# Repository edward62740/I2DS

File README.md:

# Internal Intruder Detection System (I<sup>2</sup>DS)

## Overview
This is a sub-GHz proprietary security sensor system. The sensors listed below will enter sensing mode once enabled through the [CPN GUI](https://github.com/edward62740/i2ds/blob/master/CPN%20ESP32/src/app_gui.cpp) or the [mobile app](https://github.com/edward62740/i2ds/tree/master/App). Any detected intrusion will then trigger a [FCM](https://github.com/edward62740/i2ds-fcm) background notification on the smartphones of the users with the mobile app installed.
Used in conjunction with [WMNS](https://github.com/edward62740/Wireless-Mesh-Network-System) for integrated data collection and security.

## Related/Parallel Development
[Firebase Cloud Messaging](https://github.com/edward62740/i2ds-fcm) for providing mobile notifications of security events<br>
[Google Actions + Dialogflow](https://github.com/edward62740/i2ds-assistant) to integrate with Google Home systems<br>
[Camera + tflite Person Detector](https://github.com/edward62740/i2ds-sentinel) to provide image capture and continuous on-device person detection with tensorflow lite <br>
[Firebase Responder](https://github.com/edward62740/firebase-responder) to trigger other IoT devices' actions <br>

## System Structure

#### Subnetwork
All network management and communication between sensors is restricted to this region. Some management functions are exposed to the Wi-Fi/GUI co-processor via USART.
#### Local Sensor Network
Includes the subnetwork, as well as the CPN Wi-Fi section, which is used to communicate with Firebase RTDB.
#### Mobile App
Used to control the active/inactive state of the sensors, receive status updates.<br><br>

#### FCM
Used to detect certain changes to the RTDB (i.e sensor triggered), and notify the user even if the app is not running.

 ## Sensors
 CPN             |  PIRSN      |  ACSN
:-------------------------:|:-------------------------:|:-------------------------:
<br />This is the main network controller <br> and provides a touch GUI for setting sensors|<br />This is a PIR sensor node for detecting *motion* |  <br />This is a hall-effect sensor for detecting <br> open/closed doors and windows

## Important Information
### PIRSN
* This sensor uses EKMB1110112 PIR sensor to detect motion up to a distance of 7m (indoors).
* Typical 5.5uA in sleep, avg 19uA with 2s polling and 5s reporting interval.

### ACSN
* This sensor uses the SM353LT hall effect sensor to detect when the sensor's magnet moves away (door opens).
* Typical 5.3uA in sleep, avg 19uA with 2s polling and 5s reporting interval.

### CPN
* This device contains two microcontrollers, for the sensor network [(EFR32xG23)](https://www.silabs.com/wireless/proprietary/efr32fg23-sub-ghz-wireless-soc) and Wi-Fi/GUI (ESP32). Sensor network functions are exposed to the Wi-Fi processor via USART. While there is significant traffic, in effect the only change that can be made to the sensor network is to activate/inactivate the sensors. Doing so also requires the relevant Firebase auth credentials. This provides some protection from attacks based on injecting false data into the system to incapacitate the sensor network.
* This device also provides internal battery backup with FCM notification when triggered. It is assumed that physical security beyond debug lock, encryption etc. is not crucial as the sensors would have already triggered warnings before the CPN can be tampered with. This functionality is mostly to keep the system afloat during a power outage (but this must be used with a backup 4G network or other such systems).

### Overall System
* From testing, there was a net delay of 3-4s from sensor triggered to receiving FCM notification on client smartphone. Results will vary based on Internet speeds.
* Sensors are capable of receiving messages to implement the aforementioned enabling/disabling feature. This is necessary to prevent constant triggering of the sensor when not in use, and is much more energy efficient than letting the sensor trigger all the time and filter on the coordinator side.
* The subnetwork communicates in the 915MHz ISM band, but a simple hardware swap of the chip antenna (W3211 -> W3214) allows for reconfiguration to 868MHz band. RF matching is optimized for both. Modulation/frequency is set to OQPSK 500kbps, to increase operational range set to DSSS with lower bitrate, enable FEC.
* For increased network size, where >2 hops are expected, the ACK timeout should be increased.

## Security
* The sensor HW is built around the [EFR32xG23](https://www.silabs.com/wireless/proprietary/efr32fg23-sub-ghz-wireless-soc) series, industry-leading at the time of this release, with PSA 3 level security qualifications. Anti-tamper functions are configured such that the sensor will automatically raise a warning and drop out of the network if tamper is detected.
* Sensor OTA communication is AES encrypted with [Mbed TLS](https://github.com/Mbed-TLS/mbedtls).
* Only necessary state control functions are exposed outside of the subnetwork.
* Parts of this project are not published due to security concerns. Please contact the developer for more information.

## Upkeep
* Estimated $0.00 cost from Firebase cloud functions for triggering [FCM](https://github.com/edward62740/i2ds-fcm), unless triggered more than 2 million times/month for some reason.
* More than 2 years battery life for sensors, using low-cost CR2450 cells.
* Electricity costs from CPN. Consumes less power than a night-light.

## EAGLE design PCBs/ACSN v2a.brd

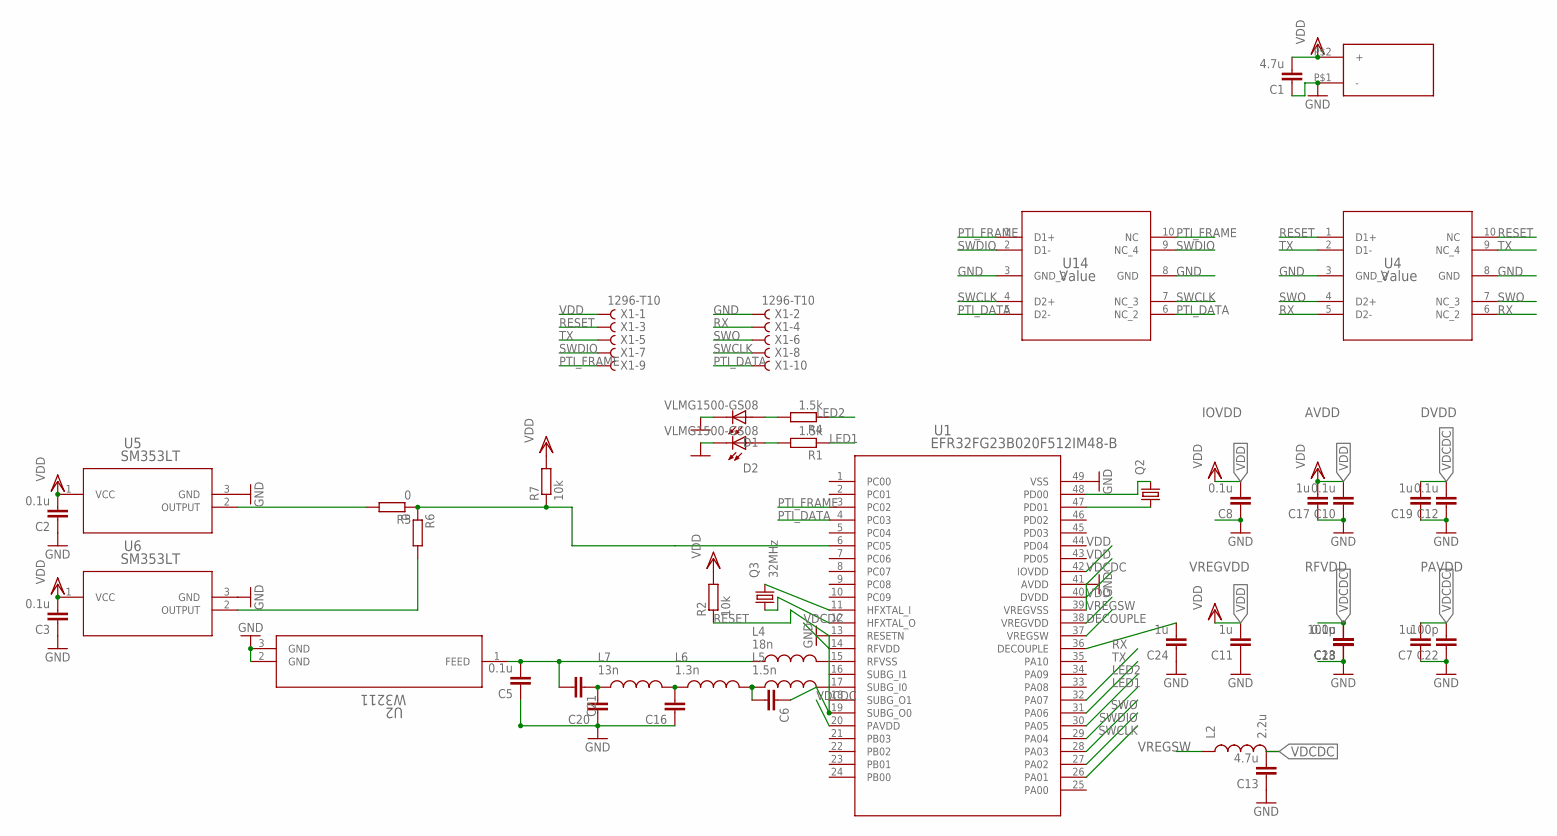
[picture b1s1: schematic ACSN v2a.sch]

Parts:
C1, C13: 4.7u; C0603R
C2, C3, C5, C8, C10, C12, C18: 0.1u; C0402
C6: 1.9p; C0402
C7, C11, C17, C19, C24: 1u; C0402
C16: 7.2p; C0402
C20: 1.3p; C0402
C21: 220p; C0402
C22, C23: 100p; C0402
D1, D2: VLMG1500-GS08; LEDC1005X35N
L2: 2.2u; L0603
L4: 18n; INDC0402X26N
L5: 1.5n; INDC0402X26N
L6: 1.3n; INDC0402X26N
L7: 13n; INDC0402X26N
Q2: KX-327-RT; 2.0X1.2
Q3: 32MHz; 2.0X1.6_KX-5
R1, R4: 1.5k; R0402
R2, R7: 10k; R0402
R5, R6: 0; R0402
U1: EFR32FG23B020F512IM48-B; QFN_48_SIL
U2: W3211; CHIP_3211_PUL
U4, U14: Value; DQA0010A
U5, U6: SM353LT; SM353LT_HNW
U$2: BS-24R; BS-24
X1: 1296-T10; 1296-10

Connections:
DECOUPLE: C24.2, U1.36 (DECOUPLE)
GND: C1.1, C2.1, C3.1, C5.1, C7.1, C8.1, C10.1, C11.1, C12.1, C13.1, C16.1, C17.1, C18.1, C19.1, C20.1, C22.1, C23.1, C24.1, D1.2, D2.2, U1.15 (RFVSS), U1.39 (VREGVSS), U1.49 (VSS), U2.2 (GND), U2.3 (GND), U4.3 (GND_2), U4.8 (GND), U5.3 (GND), U6.3 (GND), U14.3 (GND_2), U14.8 (GND), U$2.P$1 (-), X1.2
LED1: R1.1, U1.29 (PA04)
LED2: R4.1, U1.30 (PA05)
unnamed: D2.1, R1.2
unnamed: R5.1, R6.1, R7.1, U1.6 (PC05)
unnamed: C5.2, C21.2, L4.1, U2.1 (FEED)
unnamed: C6.1, L5.2, U1.19 (SUBG_O0)
unnamed: D1.1, R4.2
unnamed: R5.2, U5.2 (OUTPUT)
unnamed: R6.2, U6.2 (OUTPUT)
unnamed: Q3.3 (2), U1.11 (HFXTAL_I)
unnamed: Q3.1, U1.12 (HFXTAL_O)
unnamed: Q2.1, U1.47 (PD01)
unnamed: Q2.2, U1.48 (PD00)
unnamed: L4.2, U1.17 (SUBG_I0)
unnamed: C6.2, L5.1, L6.2
unnamed: C16.2, L6.1, L7.2
unnamed: C20.2, C21.1, L7.1
PTI_DATA: U1.4 (PC03), U14.5 (D2-), U14.6 (NC_2), X1.10
PTI_FRAME: U1.3 (PC02), U14.1 (D1+), U14.10 (NC), X1.9
RESET: R2.1, U1.13 (RESETN), U4.1 (D1+), U4.10 (NC), X1.3
RX: U1.32 (PA07), U4.5 (D2-), U4.6 (NC_2), X1.4
SWCLK: U1.26 (PA01), U14.4 (D2+), U14.7 (NC_3), X1.8
SWDIO: U1.27 (PA02), U14.2 (D1-), U14.9 (NC_4), X1.7
SWO: U1.28 (PA03), U4.4 (D2+), U4.7 (NC_3), X1.6
TX: U1.31 (PA06), U4.2 (D1-), U4.9 (NC_4), X1.5
VDCDC: C7.2, C12.2, C13.2, C18.2, C19.2, C22.2, C23.2, L2.2, U1.14 (RFVDD), U1.20 (PAVDD), U1.40 (DVDD)
VDD: C1.2, C2.2, C3.2, C8.2, C10.2, C11.2, C17.2, R2.2, R7.2, U1.38 (VREGVDD), U1.41 (AVDD), U1.42 (IOVDD), U5.1 (VCC), U6.1 (VCC), U$2.P$2 (+), X1.1
VREGSW: L2.1, U1.37 (VREGSW)

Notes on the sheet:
IOVDD
AVDD
DVDD
VREGVDD
RFVDD
PAVDD

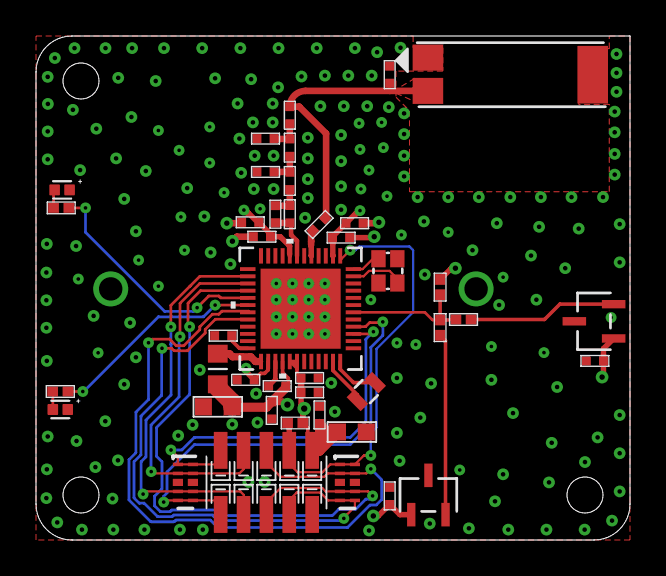
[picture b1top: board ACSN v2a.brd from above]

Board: 4 copper layers, 33.0 x 28.0 mm, 43 parts (1 on the bottom side), 30 nets.

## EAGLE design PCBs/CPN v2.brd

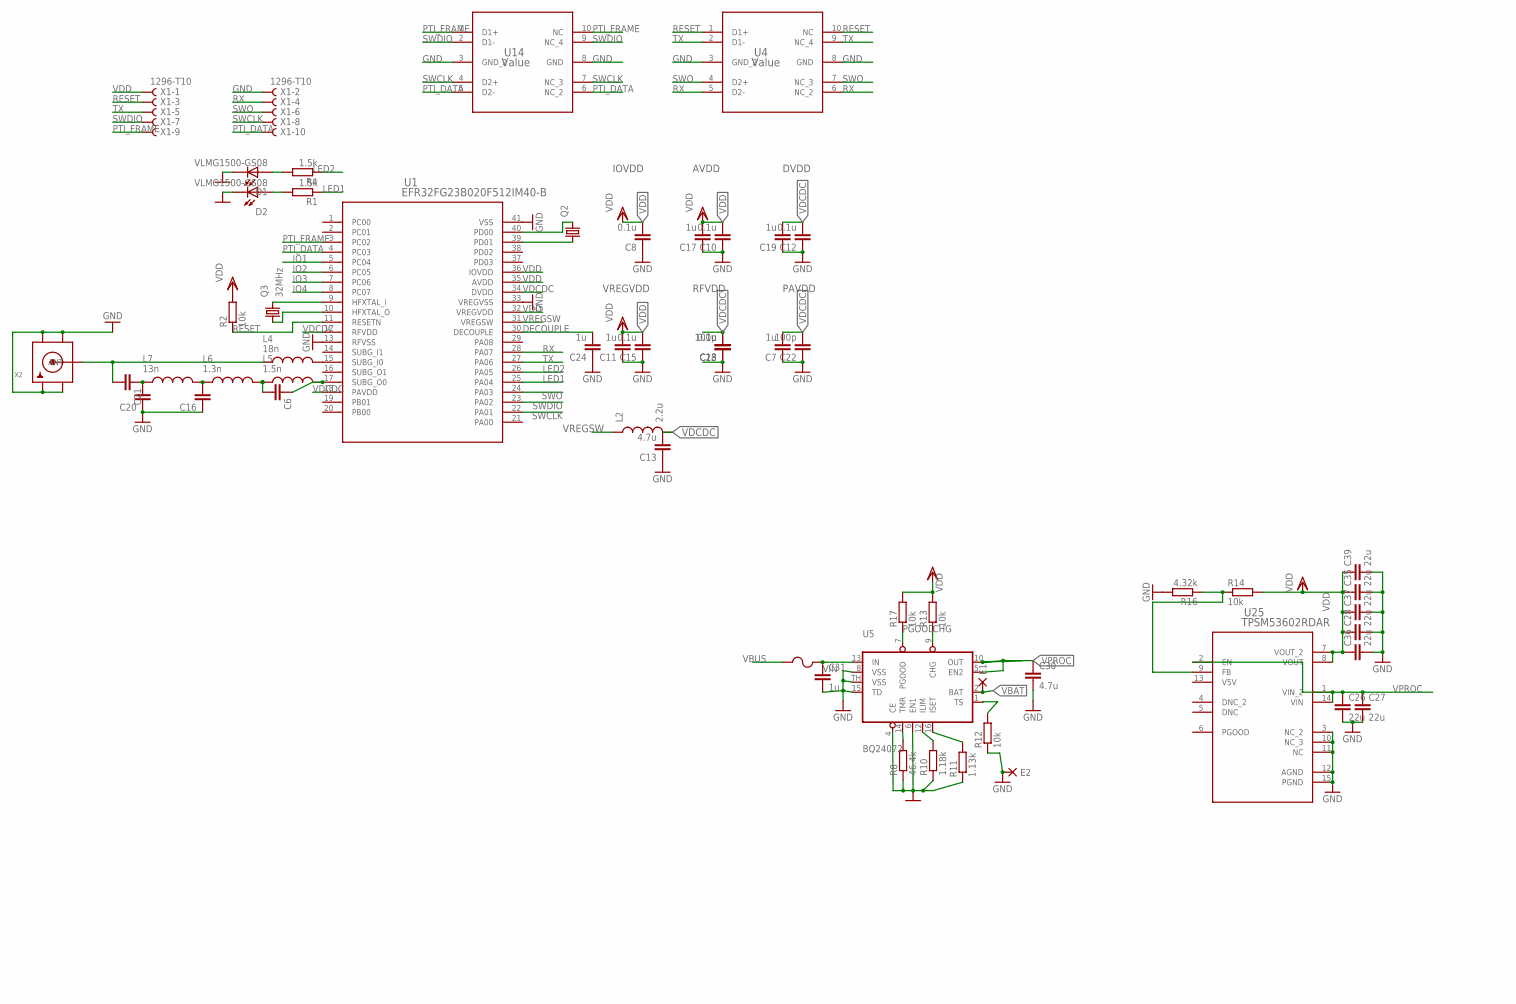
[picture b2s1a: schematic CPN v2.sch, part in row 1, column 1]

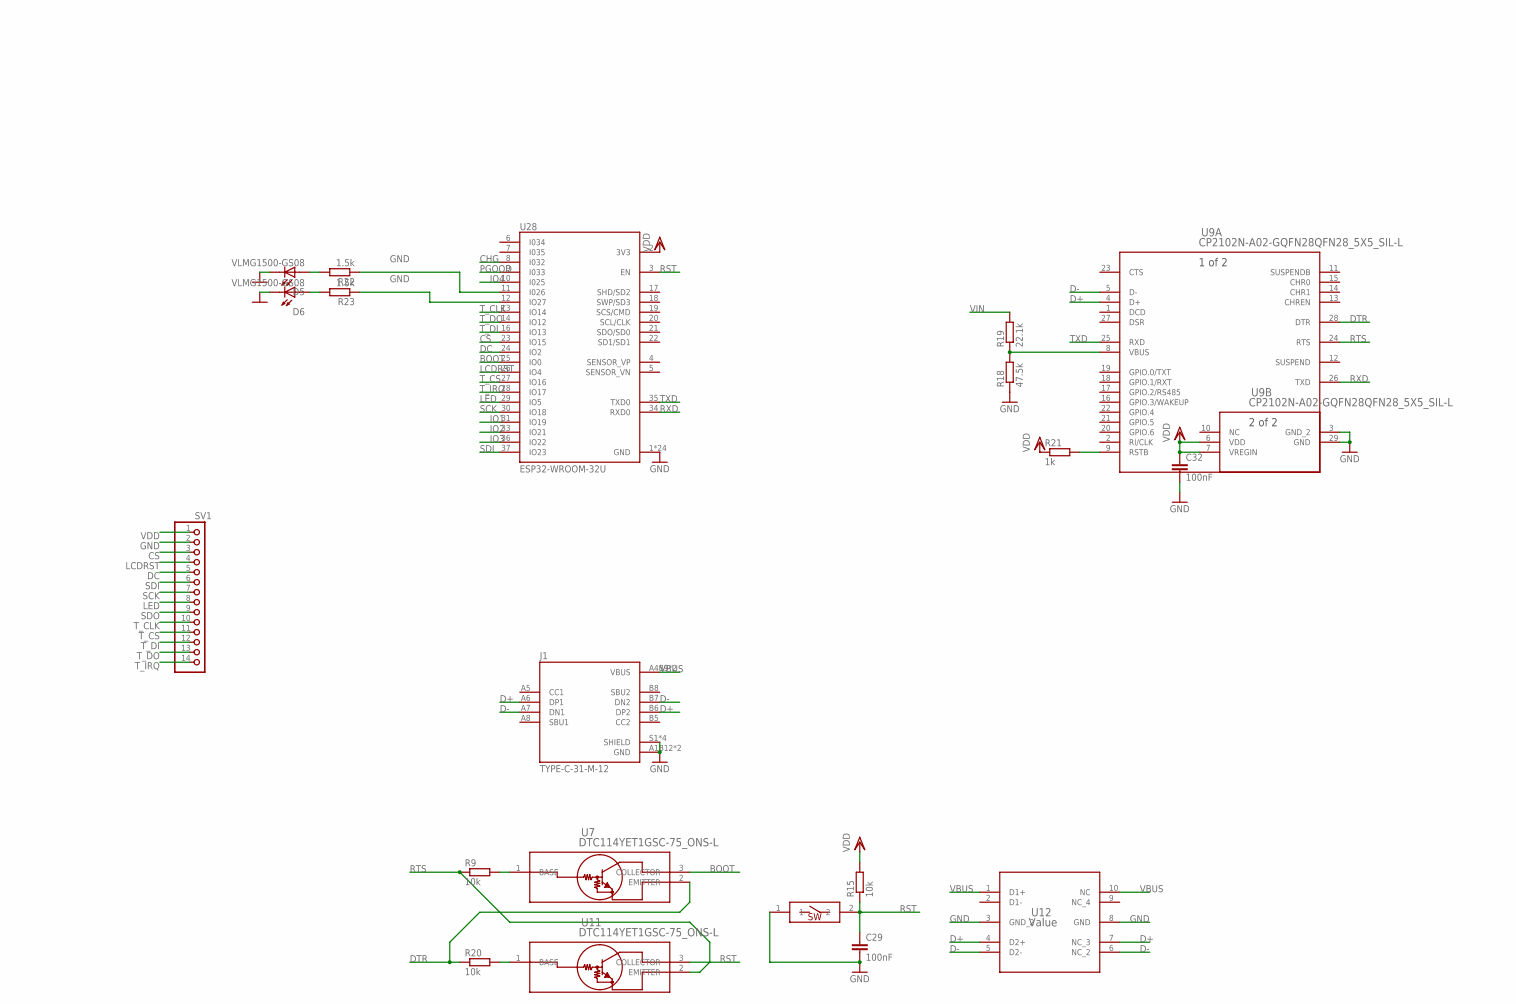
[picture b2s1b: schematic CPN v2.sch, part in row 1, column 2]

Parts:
C6: 1.9p; C0402
C7, C11, C17, C19, C24, C31: 1u; C0402
C8, C10, C12, C15, C18: 0.1u; C0402
C13: 4.7u; C0603R
C16: 7.2p; C0402
C20: 1.3p; C0402
C21: 220p; C0402
C22, C23: 100p; C0402
C26, C27, C28, C35, C36, C37, C39: 22u; C0603R
C29, C32: 100nF; C0402
C30: 4.7u; C0402
D1, D2, D5, D6: VLMG1500-GS08; LEDC1005X35N
E1, E2: DPADS_PAD-0400-S; DPADS_0400-S
F2: 1210L050YR1210LSERIES_LTF-L; 1210LSERIES_LTF-L
J1: TYPE-C-31-M-12; HRO_TYPE-C-31-M-12
L2: 2.2u; L0603
L4: 18n; INDC0402X26N
L5: 1.5n; INDC0402X26N
L6: 1.3n; INDC0402X26N
L7: 13n; INDC0402X26N
Q2: KX-327-RT; 2.0X1.2
Q3: 32MHz; 2.0X1.6_KX-5
R1, R4, R22, R23: 1.5k; R0402
R2, R9, R12, R13, R14, R15, R17, R20: 10k; R0402
R8: 46.4k; R0402
R10: 1.18k; R0402
R11: 1.13k; R0402
R16: 4.32k; R0402
R18: 47.5k; R0402
R19: 22.1k; R0402
R21: 1k; R0402
RESET: SMDSWITCH; RESC4217X170
SV1: PINHD-1X14; 1X14
U1: EFR32FG23B020F512IM40-B; QFN_40_SIL
U4, U12, U14: Value; DQA0010A
U5: BQ24072; S-PVQFN-N16
U7, U11: DTC114YET1GSC-75_ONS-L; SC-75_ONS-L
U9: CP2102N-A02-GQFN28QFN28_5X5_SIL-L; QFN28_5X5_SIL-L
U25: TPSM53602RDAR; B3QFN15_RDA_TEX
U28: ESP32-WROOM-32U; XCVR_ESP32-WROOM-32U
X1: 1296-T10; 1296-10
X2: SMACONNECTOR; SMA90_DIP

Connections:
BOOT: U7.3 (COLLECTOR), U28.25 (IO0)
CHG: R13.1, U5.9 (CHG), U28.8 (I032)
CS: SV1.3, U28.23 (IO15)
D+: J1.A6 (DP1), J1.B6 (DP2), U9.4 (D+), U12.4 (D2+), U12.7 (NC_3)
D-: J1.A7 (DN1), J1.B7 (DN2), U9.5 (D-), U12.5 (D2-), U12.6 (NC_2)
DC: SV1.5, U28.24 (IO2)
DECOUPLE: C24.2, U1.30 (DECOUPLE)
DTR: R20.1, U7.2 (EMITTER), U9.28 (DTR)
GND: C7.1, C8.1, C10.1, C11.1, C12.1, C13.1, C15.1, C16.1, C17.1, C18.1, C19.1, C20.1, C22.1, C23.1, C24.1, C26.2, C27.2, C28.2, C29.2, C30.2, C31.2, C32.2, C35.2, C36.2, C37.2, C39.2, D1.2, D2.2, D5.2, D6.2, E2.PAD, J1.A1B12 (GND), J1.B1A12 (GND), J1.S1 (SHIELD), J1.S2 (SHIELD), J1.S3 (SHIELD), J1.S4 (SHIELD), R8.1, R10.1, R11.1, R12.1, R16.2, R18.1, RESET.1, SV1.2, U1.13 (RFVSS), U1.33 (VREGVSS), U1.41 (VSS), U4.3 (GND_2), U4.8 (GND), U5.4 (CE), U5.6 (EN1), U5.8 (VSS), U5.15 (TD), U5.TH (VSS), U9.3 (GND_2), U9.29 (GND), U12.3 (GND_2), U12.8 (GND), U14.3 (GND_2), U14.8 (GND), U25.3 (NC_2), U25.10 (NC_3), U25.11 (NC), U25.12 (AGND), U25.15 (PGND), U28.1 (GND), U28.15 (GND), U28.38 (GND), U28.G.1 (GND), U28.G.2 (GND), U28.G.4 (GND), U28.G.5 (GND), U28.G.6 (GND), U28.G.7 (GND), U28.G.8 (GND), U28.G.9 (GND), U28.G.10 (GND), U28.G.11 (GND), U28.G.12 (GND), U28.G.13 (GND), U28.G.14 (GND), U28.G.15 (GND), U28.G.16 (GND), U28.G.17 (GND), U28.G.18 (GND), U28.G.19 (GND), U28.G.20 (GND), U28.G.21 (GND), U28.G.22 (GND), X1.2, X2.GND1, X2.GND2, X2.GND3, X2.GND4
IO1: U1.5 (PC04), U28.31 (IO19)
IO2: U1.6 (PC05), U28.33 (IO21)
IO3: U1.7 (PC06), U28.36 (IO22)
IO4: U1.8 (PC07), U28.10 (I025)
LCDRST: SV1.4, U28.26 (IO4)
LED: SV1.8, U28.29 (IO5)
LED1: R1.1, U1.25 (PA04)
LED2: R4.1, U1.26 (PA05)
unnamed: D2.1, R1.2
unnamed: C21.2, L4.1, X2.ANTENNA (ANT)
unnamed: C6.1, L5.2, U1.17 (SUBG_O0)
unnamed: D1.1, R4.2
unnamed: R8.2, U5.14 (TMR)
unnamed: R10.2, U5.12 (ILIM)
unnamed: R11.2, U5.16 (ISET)
unnamed: R18.2, R19.1, U9.8 (VBUS)
unnamed: R21.2, U9.9 (RSTB)
unnamed: Q3.3 (2), U1.9 (HFXTAL_I)
unnamed: Q3.1, U1.10 (HFXTAL_O)
unnamed: Q2.1, U1.39 (PD01)
unnamed: Q2.2, U1.40 (PD00)
unnamed: L4.2, U1.15 (SUBG_I0)
unnamed: D5.1, R22.2
unnamed: C6.2, L5.1, L6.2
unnamed: C16.2, L6.1, L7.2
unnamed: C20.2, C21.1, L7.1
unnamed: D6.1, R23.2
unnamed: R23.1, U28.12 (IO27)
unnamed: R22.1, U28.11 (I026)
unnamed: R20.2, U11.1 (BASE)
unnamed: R9.2, U7.1 (BASE)
unnamed: R14.1, R16.1, U25.9 (FB)
PGOOD: R17.1, U5.7 (PGOOD), U28.9 (I033)
PTI_DATA: U1.4 (PC03), U14.5 (D2-), U14.6 (NC_2), X1.10
PTI_FRAME: U1.3 (PC02), U14.1 (D1+), U14.10 (NC), X1.9
RESET: R2.1, U1.11 (RESETN), U4.1 (D1+), U4.10 (NC), X1.3
RST: C29.1, R15.1, RESET.2, U11.3 (COLLECTOR), U28.3 (EN)
RTS: R9.1, U9.24 (RTS), U11.2 (EMITTER)
RX: U1.28 (PA07), U4.5 (D2-), U4.6 (NC_2), X1.4
RXD: U9.26 (TXD), U28.34 (RXD0)
SCK: SV1.7, U28.30 (IO18)
SDI: SV1.6, U28.37 (IO23)
SDO: SV1.9
SWCLK: U1.22 (PA01), U14.4 (D2+), U14.7 (NC_3), X1.8
SWDIO: U1.23 (PA02), U14.2 (D1-), U14.9 (NC_4), X1.7
SWO: U1.24 (PA03), U4.4 (D2+), U4.7 (NC_3), X1.6
TS: R12.2, U5.1 (TS)
TX: U1.27 (PA06), U4.2 (D1-), U4.9 (NC_4), X1.5
TXD: U9.25 (RXD), U28.35 (TXD0)
T_CLK: SV1.10, U28.13 (IO14)
T_CS: SV1.11, U28.27 (IO16)
T_DI: SV1.12, U28.16 (IO13)
T_DO: SV1.13, U28.14 (IO12)
T_IRQ: SV1.14, U28.28 (IO17)
VBAT: E1.PAD, U5.2 (BAT)
VBUS: F2.1, J1.A4B9 (VBUS), J1.B4A9 (VBUS), U12.1 (D1+), U12.10 (NC)
VDCDC: C7.2, C12.2, C13.2, C18.2, C19.2, C22.2, C23.2, L2.2, U1.12 (RFVDD), U1.18 (PAVDD), U1.34 (DVDD)
VDD: C8.2, C10.2, C11.2, C15.2, C17.2, C28.1, C32.1, C35.1, C36.1, C37.1, C39.1, R2.2, R13.2, R14.2, R15.2, R17.2, R21.1, SV1.1, U1.32 (VREGVDD), U1.35 (AVDD), U1.36 (IOVDD), U9.6 (VDD), U9.7 (VREGIN), U25.7 (VOUT_2), U25.8 (VOUT), U28.2 (3V3), X1.1
VIN: C31.1, F2.2, R19.2, U5.13 (IN)
VPROC: C26.1, C27.1, C30.1, U5.5 (EN2), U5.10 (OUT), U25.1 (VIN_2), U25.2 (EN), U25.14 (VIN)
VREGSW: L2.1, U1.31 (VREGSW)

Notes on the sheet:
IOVDD
AVDD
DVDD
VREGVDD
RFVDD
PAVDD

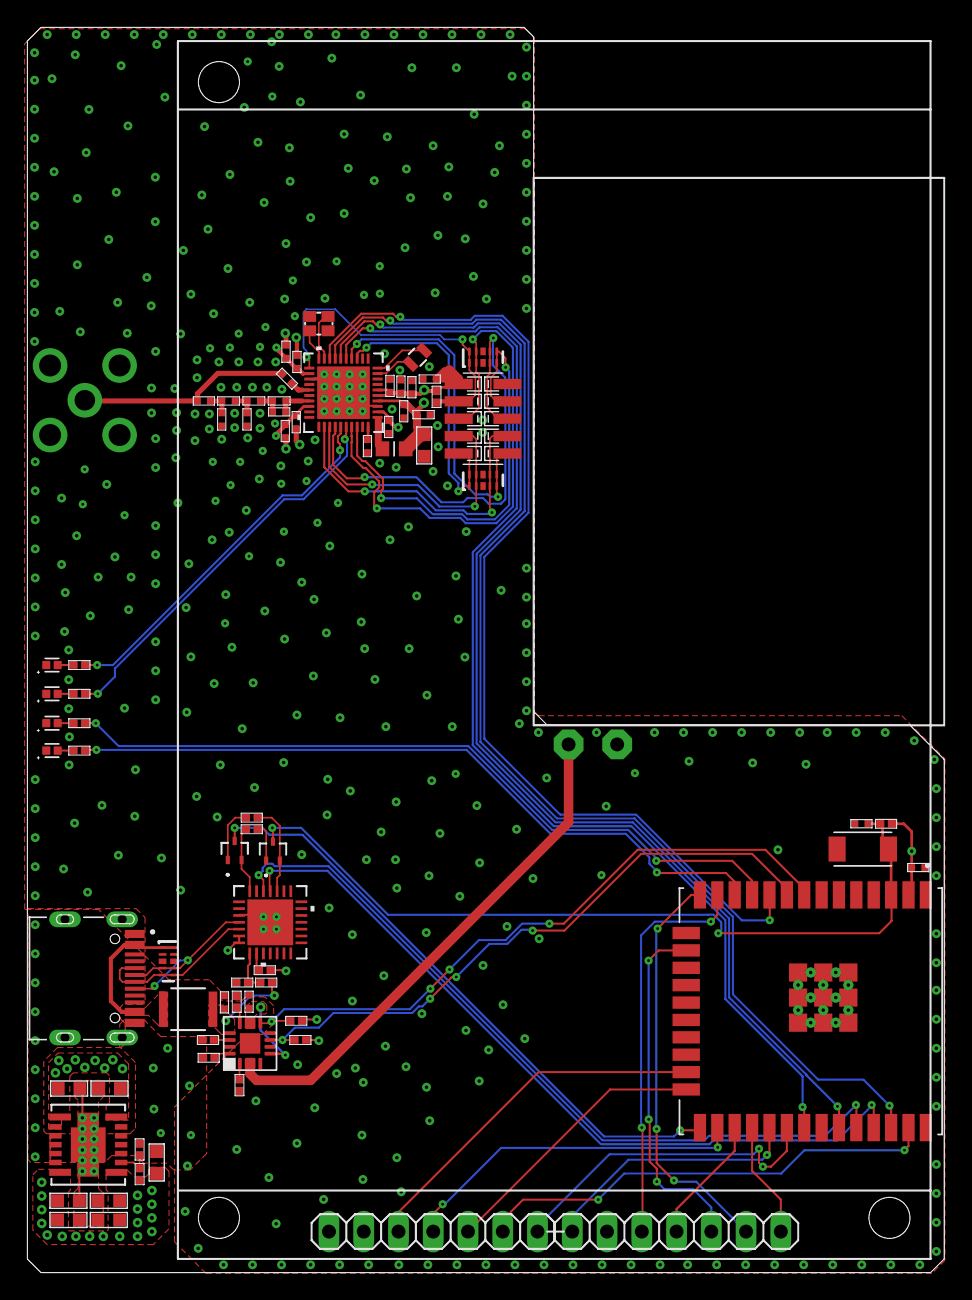
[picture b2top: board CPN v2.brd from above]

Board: 4 copper layers, 67.0 x 91.0 mm, 76 parts (0 on the bottom side), 69 nets.

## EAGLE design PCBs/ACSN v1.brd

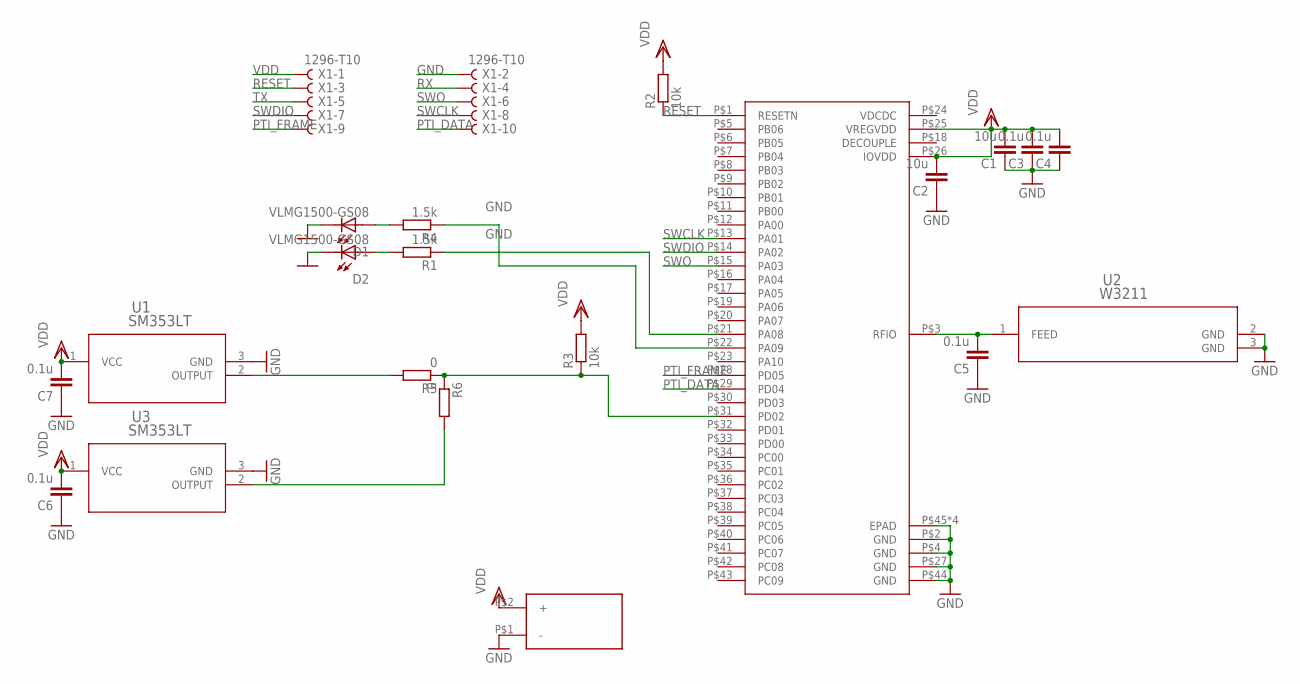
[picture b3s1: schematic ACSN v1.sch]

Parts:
C1, C2: 10u; C0603R
C3, C4, C5, C6, C7: 0.1u; C0402
D1, D2: VLMG1500-GS08; LEDC1005X35N
R1, R4: 1.5k; R0402
R2, R3: 10k; R0402
R5, R6: 0; R0402
U1, U3: SM353LT; SM353LT_HNW
U2: W3211; CHIP_3211_PUL
U$1: ZGM230S
U$2: BS-24R; BS-24
X1: 1296-T10; 1296-10

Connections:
GND: C1.1, C2.1, C3.1, C4.1, C5.1, C6.1, C7.1, D1.2, D2.2, U1.3 (GND), U2.2 (GND), U2.3 (GND), U3.3 (GND), U$1.P$2 (GND), U$1.P$4 (GND), U$1.P$27 (GND), U$1.P$44 (GND), U$1.P$45 (EPAD), U$1.P$46 (EPAD), U$1.P$47 (EPAD), U$1.P$48 (EPAD), U$2.P$1 (-), X1.2
unnamed: D2.1, R1.2
unnamed: R1.1, U$1.P$21 (PA08)
unnamed: R4.1, U$1.P$22 (PA09)
unnamed: C5.2, U2.1 (FEED), U$1.P$3 (RFIO)
unnamed: R3.1, R5.1, R6.1, U$1.P$31 (PD02)
unnamed: D1.1, R4.2
unnamed: R5.2, U1.2 (OUTPUT)
unnamed: R6.2, U3.2 (OUTPUT)
PTI_DATA: U$1.P$29 (PD04), X1.10
PTI_FRAME: U$1.P$28 (PD05), X1.9
RESET: R2.1, U$1.P$1 (RESETN), X1.3
RX: X1.4
SWCLK: U$1.P$13 (PA01), X1.8
SWDIO: U$1.P$14 (PA02), X1.7
SWO: U$1.P$15 (PA03), X1.6
TX: X1.5
VDD: C1.2, C2.2, C3.2, C4.2, C6.2, C7.2, R2.2, R3.2, U1.1 (VCC), U3.1 (VCC), U$1.P$25 (VREGVDD), U$1.P$26 (IOVDD), U$2.P$2 (+), X1.1

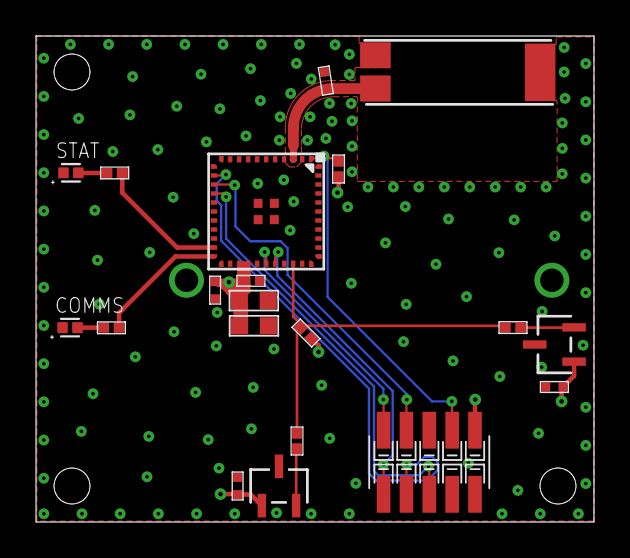
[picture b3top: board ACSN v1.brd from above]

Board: 4 copper layers, 31.0 x 27.0 mm, 21 parts (1 on the bottom side), 16 nets.

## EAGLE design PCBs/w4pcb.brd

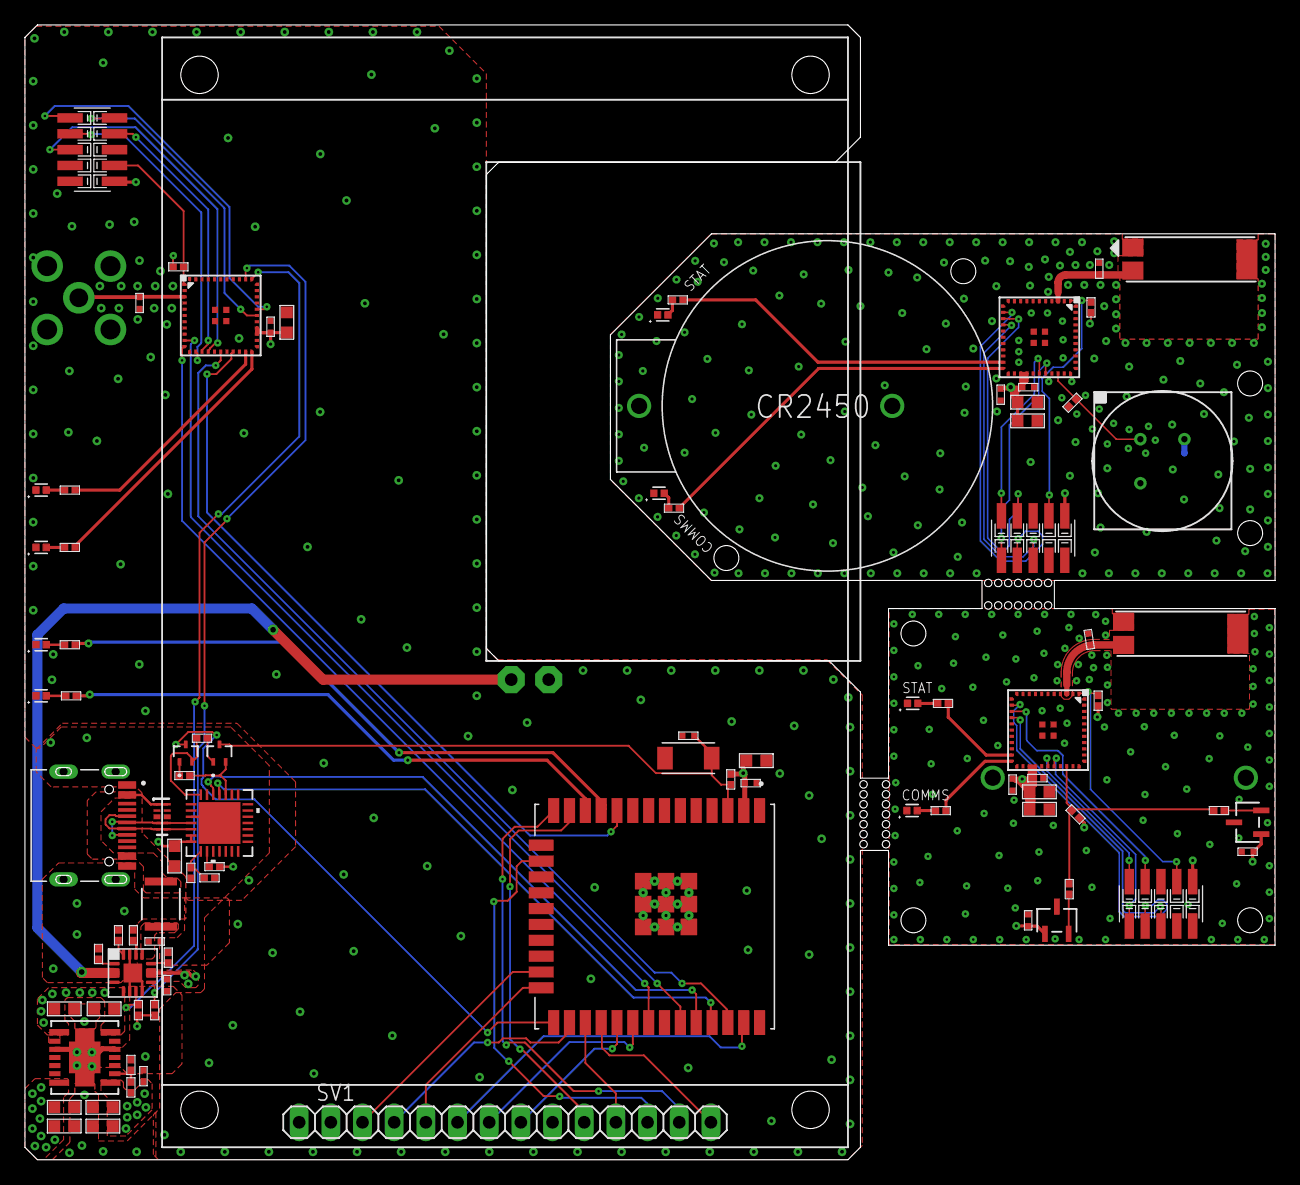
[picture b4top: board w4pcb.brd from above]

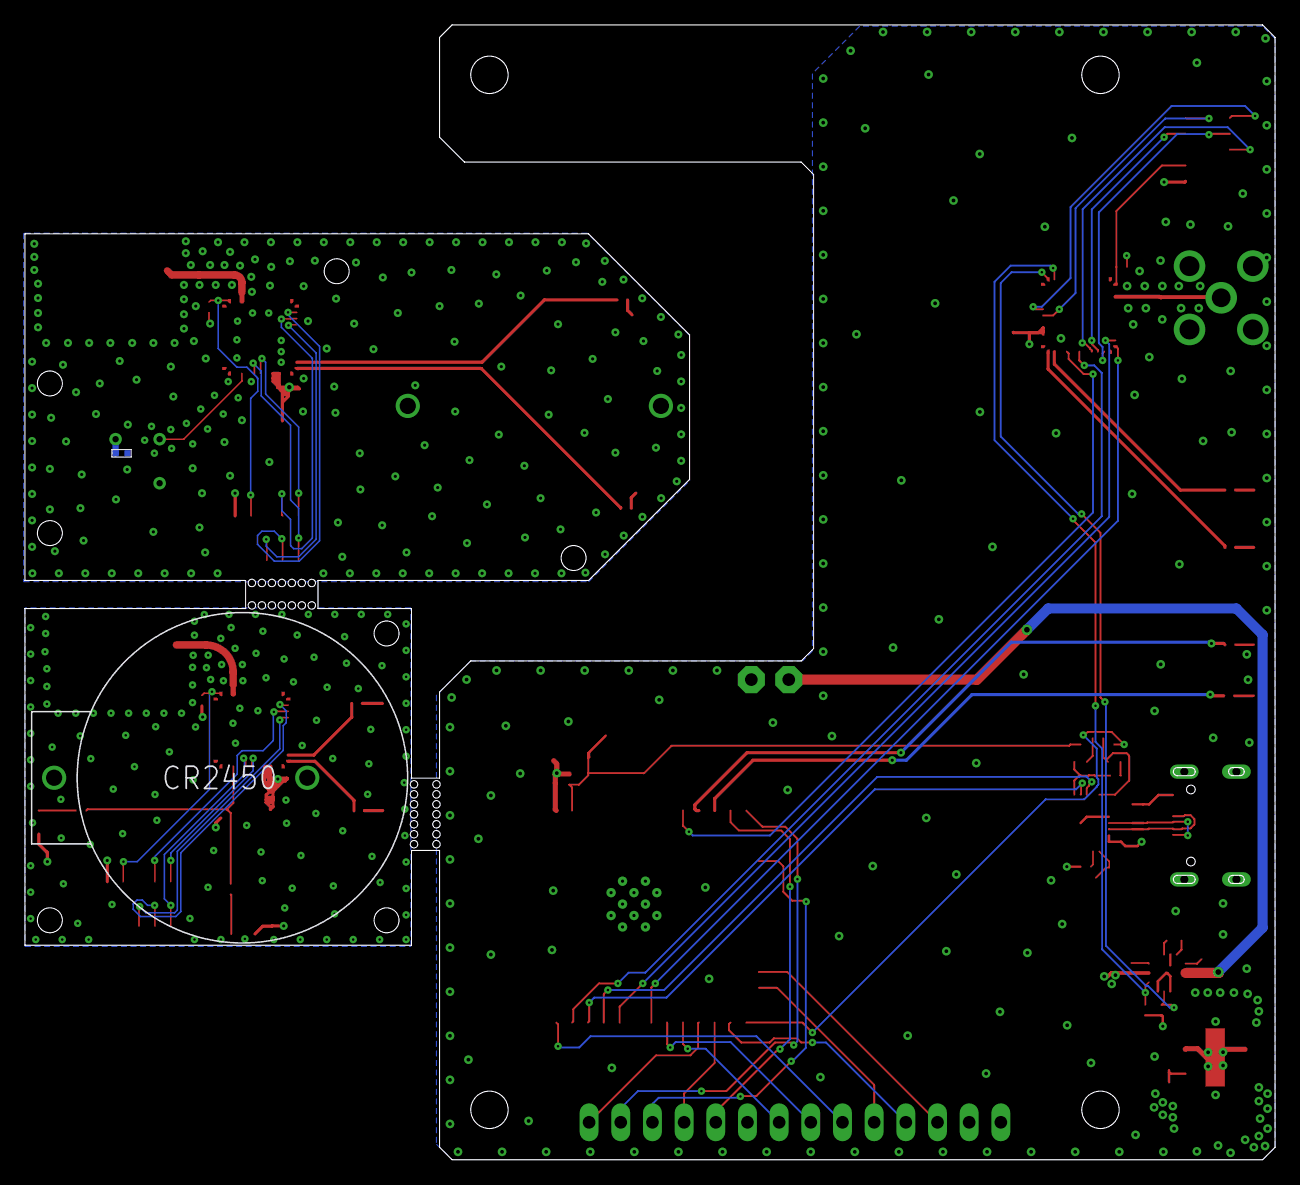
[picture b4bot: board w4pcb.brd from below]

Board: 4 copper layers, 100.2 x 91.0 mm, 93 parts (2 on the bottom side), 85 nets.

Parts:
C1, C2, C7, C8, C14, C15: 10u; C0603R
C3, C4, C5, C6, C9, C10, C11, C12, C13, C16, C17, C18: 0.1u; C0402
C19, C20, C21, C35, C36, C37, C39: 22u; C0603R
C22: 4.7u; C0402
C23: 1u; C0402
C24, C25: 100nF; C0402
D1, D2, D3, D4, D5, D6, D7, D8: VLMG1500-GS08; LEDC1005X35N
E1, E2: DPADS_PAD-0400-S; DPADS_0400-S
F2: 1210L050YR1210LSERIES_LTF-L; 1210LSERIES_LTF-L
J1: TYPE-C-31-M-12; HRO_TYPE-C-31-M-12
R1, R4, R5, R7, R12, R13, R28, R29: 1.5k; R0402
R2, R3, R6, R10, R11, R14, R15, R17, R20, R22, R23, R24: 10k; R0402
R8, R9: 0; R0402
R16: 4.32k; R0402
R18: 46.4k; R0402
R19: 1.18k; R0402
R21: 1.13k; R0402
R25: 47.5k; R0402
R26: 22.1k; R0402
R27: 1k; R0402
RESET: SMDSWITCH; RESC4217X170
SV1: 1X14
U1, U5: SM353LT; SM353LT_HNW
U2, U4: W3211; CHIP_3211_PUL
U3: EKMB1201111; SENSOR_B1201111_PAN
U6: BQ24072; S-PVQFN-N16
U7, U11: DTC114YET1GSC-75_ONS-L; SC-75_ONS-L
U9: CP2102N-A02-GQFN28QFN28_5X5_SIL-L; QFN28_5X5_SIL-L
U12: Value; DQA0010A
U25: TPSM53602RDAR; B3QFN15_RDA_TEX
U28: ESP32-WROOM-32U; XCVR_ESP32-WROOM-32U
U$1, U$3, U$5: ZGM230S
U$2, U$4: BS-24R; BS-24
X1, X2, X4: 1296-T10; 1296-10
X3: SMA90_DIP

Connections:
BOOT: U7.3, U28.25
CHG: R23.1, U6.9, U$5.P$35
CS: SV1.3, U28.23
D+: J1.A6, J1.B6, U9.4, U12.4, U12.7
D-: J1.A7, J1.B7, U9.5, U12.5, U12.6
DC: SV1.5, U28.24
DTR: R20.1, U7.2, U9.28
GND: C1.1, C2.1, C3.1, C4.1, C5.1, C6.1, D1.2, D2.2, R3.1, U2.2, U2.3, U3.1, U$1.P$2, U$1.P$4, U$1.P$27, U$1.P$44, U$1.P$45, U$1.P$46, U$1.P$47, U$1.P$48, U$2.P$1, X1.2
GND1: C7.1, C8.1, C9.1, C10.1, C11.1, C12.1, C13.1, D3.2, D4.2, U1.3, U4.2, U4.3, U5.3, U$3.P$2, U$3.P$4, U$3.P$27, U$3.P$44, U$3.P$45, U$3.P$46, U$3.P$47, U$3.P$48, U$4.P$1, X2.2
GND3: C14.1, C15.1, C16.1, C17.1, C18.1, C19.2, C20.2, C21.2, C22.2, C23.2, C24.2, C25.2, C35.2, C36.2, C37.2, C39.2, D5.2, D6.2, D7.2, D8.2, E2.PAD, J1.A1B12, J1.B1A12, J1.S1, J1.S2, J1.S3, J1.S4, R16.2, R18.1, R19.1, R21.1, R22.1, R25.1, RESET.1, SV1.2, U6.4, U6.6, U6.8, U6.15, U6.TH, U9.3, U9.29, U12.3, U12.8, U25.3, U25.10, U25.11, U25.12, U25.15, U28.1, U28.15, U28.38, U28.G.1, U28.G.2, U28.G.4, U28.G.5, U28.G.6, U28.G.7, U28.G.8, U28.G.9, U28.G.10, U28.G.11, U28.G.12, U28.G.13, U28.G.14, U28.G.15, U28.G.16, U28.G.17, U28.G.18, U28.G.19, U28.G.20, U28.G.21, U28.G.22, U$5.P$2, U$5.P$4, U$5.P$27, U$5.P$44, U$5.P$45, U$5.P$46, U$5.P$47, U$5.P$48, X3.GND1, X3.GND2, X3.GND3, X3.GND4, X4.2
IO1: U28.31, U$5.P$11
IO2: U28.33, U$5.P$10
IO3: U28.36, U$5.P$17
IO4: U28.10, U$5.P$19
LCDRST: SV1.4, U28.26
LED: SV1.8, U28.29
unnamed: D2.1, R1.2
unnamed: R1.1, U$1.P$21
unnamed: R4.1, U$1.P$22
unnamed: R3.2, U3.2, U$1.P$31
unnamed: C5.2, U2.1, U$1.P$3
unnamed: C11.2, U4.1, U$3.P$3
unnamed: D1.1, R4.2
unnamed: D3.1, R7.2
unnamed: D4.1, R5.2
unnamed: R5.1, U$3.P$21
unnamed: R7.1, U$3.P$22
unnamed: R8.1, R9.1, R10.1, U$3.P$31
unnamed: R8.2, U1.2
unnamed: R9.2, U5.2
unnamed: C18.2, U$5.P$3, X3.ANTENNA
unnamed: D5.1, R12.2
unnamed: D6.1, R13.2
unnamed: R13.1, U$5.P$21
unnamed: R12.1, U$5.P$22
unnamed: R18.2, U6.14
unnamed: R19.2, U6.12
unnamed: R21.2, U6.16
unnamed: R25.2, R26.1, U9.8
unnamed: R27.2, U9.9
unnamed: D7.1, R28.2
unnamed: D8.1, R29.2
unnamed: R29.1, U28.12
unnamed: R28.1, U28.11
unnamed: R20.2, U11.1
unnamed: R17.2, U7.1
unnamed: R14.1, R16.1, U25.9
PGOOD: R24.1, U6.7, U$5.P$34
PTI_DATA: U$1.P$29, X1.10
PTI_DATA1: U$3.P$29, X2.10
PTI_DATA2: U$5.P$29, X4.10
PTI_FRAME: U$1.P$28, X1.9
PTI_FRAME1: U$3.P$28, X2.9
PTI_FRAME2: U$5.P$28, X4.9
RESET: R2.1, U$1.P$1, X1.3
RESET1: R6.1, U$3.P$1, X2.3
RESET2: R11.1, U$5.P$1, X4.3
RST: C25.1, R15.1, RESET.2, U11.3, U28.3
RTS: R17.1, U9.24, U11.2
RXD: U9.26, U28.34
SCK: SV1.7, U28.30
SDI: SV1.6, U28.37
SWCLK: U$1.P$13, X1.8
SWCLK1: U$3.P$13, X2.8
SWCLK2: U$5.P$13, X4.8
SWDIO: U$1.P$14, X1.7
SWDIO1: U$3.P$14, X2.7
SWDIO2: U$5.P$14, X4.7
SWO: U$1.P$15, X1.6
SWO1: U$3.P$15, X2.6
SWO2: U$5.P$15, X4.6
TS: R22.2, U6.1
TXD: U9.25, U28.35
T_CLK: SV1.10, U28.13
T_CS: SV1.11, U28.27
T_DI: SV1.12, U28.16
T_DO: SV1.13, U28.14
T_IRQ: SV1.14, U28.28
VBAT: E1.PAD, U6.2
VBUS: F2.1, J1.A4B9, J1.B4A9, U12.1, U12.10
VDD: C1.2, C2.2, C3.2, C4.2, C6.2, R2.2, U3.3, U$1.P$25, U$1.P$26, U$2.P$2, X1.1
VDD1: C7.2, C8.2, C9.2, C10.2, C12.2, C13.2, R6.2, R10.2, U1.1, U5.1, U$3.P$25, U$3.P$26, U$4.P$2, X2.1
VDD2: C14.2, C15.2, C16.2, C17.2, C21.1, C24.1, C35.1, C36.1, C37.1, C39.1, R11.2, R14.2, R15.2, R23.2, R24.2, R27.1, SV1.1, U9.6, U9.7, U25.7, U25.8, U28.2, U$5.P$25, U$5.P$26, X4.1
VIN: C23.1, F2.2, U6.13
VPROC: C19.1, C20.1, C22.1, U6.5, U6.10, U25.1, U25.2, U25.14

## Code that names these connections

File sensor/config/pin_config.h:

#ifndef PIN_CONFIG_H
#define PIN_CONFIG_H

// $[CMU]
// [CMU]$

// $[LFXO]
// [LFXO]$

// $[PRS.ASYNCH0]
// [PRS.ASYNCH0]$

// $[PRS.ASYNCH1]
// [PRS.ASYNCH1]$

// $[PRS.ASYNCH2]
// [PRS.ASYNCH2]$

// $[PRS.ASYNCH3]
// [PRS.ASYNCH3]$

// $[PRS.ASYNCH4]
// [PRS.ASYNCH4]$

// $[PRS.ASYNCH5]
// [PRS.ASYNCH5]$

// $[PRS.ASYNCH6]
// [PRS.ASYNCH6]$

// $[PRS.ASYNCH7]
// [PRS.ASYNCH7]$

// $[PRS.ASYNCH8]
// [PRS.ASYNCH8]$

// $[PRS.ASYNCH9]
// [PRS.ASYNCH9]$

// $[PRS.ASYNCH10]
// [PRS.ASYNCH10]$

// $[PRS.ASYNCH11]
// [PRS.ASYNCH11]$

// $[PRS.SYNCH0]
// [PRS.SYNCH0]$

// $[PRS.SYNCH1]
// [PRS.SYNCH1]$

// $[PRS.SYNCH2]
// [PRS.SYNCH2]$

// $[PRS.SYNCH3]
// [PRS.SYNCH3]$

// $[GPIO]
// [GPIO]$

// $[TIMER0]
// [TIMER0]$

// $[TIMER1]
// [TIMER1]$

// $[TIMER2]
// [TIMER2]$

// $[TIMER3]
// [TIMER3]$

// $[TIMER4]
// [TIMER4]$

// $[USART0]
// [USART0]$

// $[I2C1]
// I2C1 SCL on PC05
#define I2C1_SCL_PORT                            gpioPortC
#define I2C1_SCL_PIN                             5

// I2C1 SDA on PC07
#define I2C1_SDA_PORT                            gpioPortC
#define I2C1_SDA_PIN                             7

// [I2C1]$

// $[EUSART1]
// [EUSART1]$

// $[EUSART2]
// [EUSART2]$

// $[LCD]
// [LCD]$

// $[KEYSCAN]
// [KEYSCAN]$

// $[LETIMER0]
// [LETIMER0]$

// $[ACMP0]
// [ACMP0]$

// $[ACMP1]
// [ACMP1]$

// $[VDAC0]
// [VDAC0]$

// $[PCNT0]
// [PCNT0]$

// $[LESENSE]
// [LESENSE]$

// $[HFXO0]
// [HFXO0]$

// $[I2C0]
// [I2C0]$

// $[EUSART0]
// EUSART0 CTS on PA10
#define EUSART0_CTS_PORT                         gpioPortA
#define EUSART0_CTS_PIN                          10

// EUSART0 RTS on PA00
#define EUSART0_RTS_PORT                         gpioPortA
#define EUSART0_RTS_PIN                          0

// EUSART0 RX on PA09
#define EUSART0_RX_PORT                          gpioPortA
#define EUSART0_RX_PIN                           9

// EUSART0 TX on PA08
#define EUSART0_TX_PORT                          gpioPortA
#define EUSART0_TX_PIN                           8

// [EUSART0]$

// $[PTI]
// [PTI]$

// $[MODEM]
// [MODEM]$

// $[CUSTOM_PIN_NAME]
// [CUSTOM_PIN_NAME]$

#endif // PIN_CONFIG_H

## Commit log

2022-02-09 Remove compiler files
2022-02-09 Added PCB files
2022-03-23 test
2022-03-23 added IADC PRS battery measurement feature
2022-03-24 Added lesense
2022-03-25 updated lesense, cpn init
2022-03-27 Init migrate hw
2022-03-27 update hw
2022-03-29 update em
2022-03-31 updated app
2022-04-01 updated pairing:
2022-04-07 update comms
2022-04-09 added acsn and updated comms
2022-04-10 updated ips and radio comms
2022-04-16 update cpn
2022-04-17 updated cpn, added gui
2022-04-19 updated cpn, added acsn branch
2022-04-22 added firebase to cpn
2022-05-04 added submodule i2ds-fcm
2022-05-04 updated docu
2022-05-06 clean
2022-05-06 update fcm
2022-05-13 Clean Pre-Release (v1.0)
2022-05-14 Update docu
2022-06-15 Update documentation
2022-06-21 Updated CPN fw to v1.1
2022-07-14 Update files to integrate i2ds-sentinel
2022-08-23 Finalized documentation
2022-09-29 Updated to v2.1
2022-09-29 Fix ci build (#17)
    * Update FB_Error.h
    * Update Signer.cpp

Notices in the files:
parts and their libraries:
COPYRIGHT: Copyright (C) 2022 Ultra Librarian. All rights reserved.
crystal-geyer_V1_0: Copyright: Geyer-Electronic
COPYRIGHT: Copyright (C) 2018 Accelerated Designs. All rights reserved
